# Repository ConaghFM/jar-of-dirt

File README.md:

# Jar of Dirt
- This is a simple LM386 based amplifier
- Intended to be built into a jar or other container
- For use as a miniature guitar amplifier
- Power with 9-12v DC or 9v Battery\
Designed using KiCad v4, updated to v5 28.08.2020\

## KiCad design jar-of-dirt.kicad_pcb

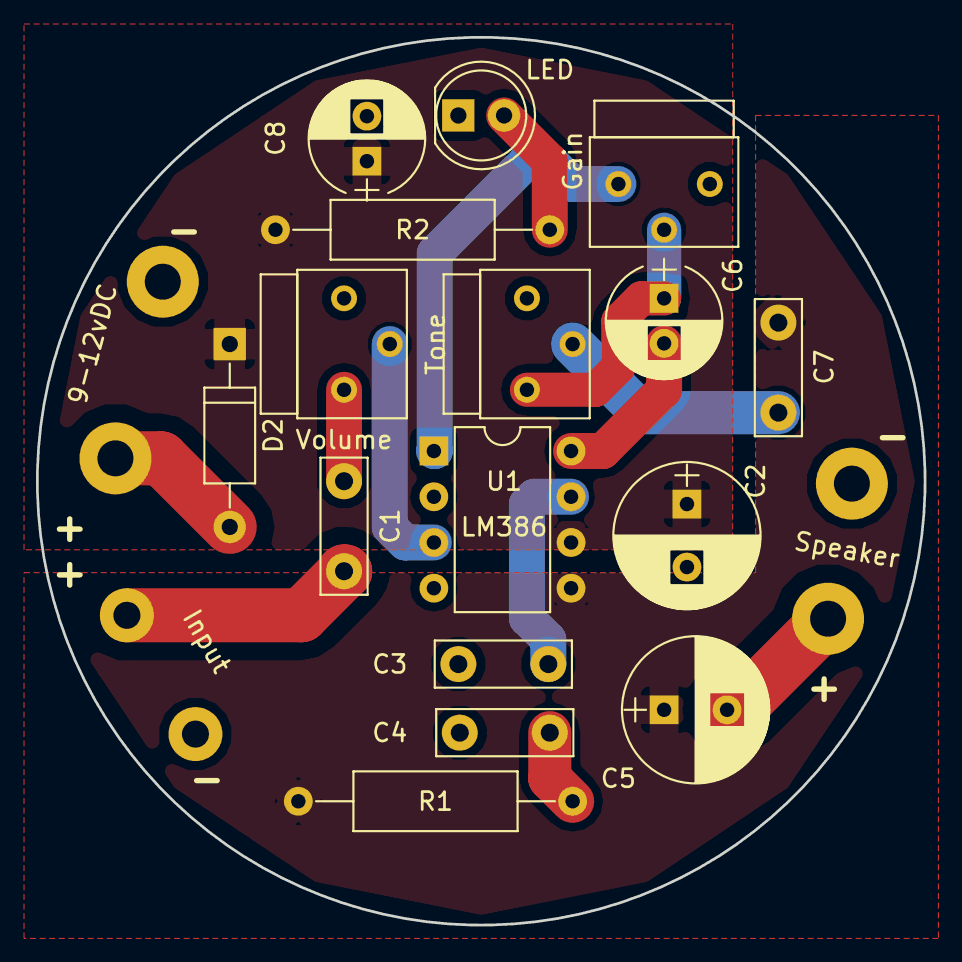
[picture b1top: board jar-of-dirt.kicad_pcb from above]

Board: 2 copper layers, 49.3 x 49.3 mm, 19 parts (0 on the bottom side), 15 nets.

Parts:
BT1: 9-12vDC; WireConnection_2.00mmDrill
C1, C3: 100n; C_Disc_D7.5mm_W2.5mm_P5.00mm
C2, C5: 220u; CP_Radial_D8.0mm_P3.50mm
C4: 47n; C_Disc_D7.5mm_W2.5mm_P5.00mm
C6, C8: 10u; CP_Radial_D6.3mm_P2.50mm
C7: 33n; C_Disc_D7.5mm_W2.5mm_P5.00mm
D1: LED; LED_D5.0mm
D2: 1N4001; D_A-405_P10.16mm_Horizontal
Gain: 10k; Potentiometer_Trimmer_Bourns_3339S_Vertical
J1: Input; WireConnection_1.50mmDrill
LS1: Speaker; WireConnection_2.00mmDrill
R1: 10; R_Axial_DIN0309_L9.0mm_D3.2mm_P15.24mm_Horizontal
R2: 470; R_Axial_DIN0309_L9.0mm_D3.2mm_P15.24mm_Horizontal
Tone: 10k; Potentiometer_Trimmer_Bourns_3339S_Vertical
U1: LM386; DIP-8_W7.62mm
Volume: 10k; Potentiometer_Trimmer_Bourns_3339S_Vertical

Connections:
GND: BT1.2, C2.2, C3.1, C4.2, C8.2, D1.1, J1.2, LS1.2, U1.2, U1.4, Volume.3
unnamed: BT1.1, D2.2
unnamed: C1.1, Volume.1
unnamed: C1.2, J1.1
unnamed: C2.1, C8.1, D2.1, R2.2, U1.6
unnamed: C3.2, U1.7
unnamed: C4.1, R1.2
unnamed: C5.1, C7.2, R1.1, U1.5
unnamed: C5.2, LS1.1
unnamed: C6.1, Gain.2, Tone.1
unnamed: C6.2, U1.8
unnamed: C7.1, Tone.2
unnamed: D1.2, R2.1
unnamed: Gain.1, U1.1
unnamed: U1.3, Volume.2

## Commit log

2020-08-23 V1.0 - as fabricated 23. Aug. 2020
2020-08-23 Added README.md
2020-08-23 added renders
2020-08-27 Updated to KiCad 5
2020-08-28 added gitignore
